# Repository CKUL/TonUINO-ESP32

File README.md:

# [TonUINO-ESP32](http://discourse.voss.earth/t/esp32-port-inkl-webinterface/399)
_[TonUINO V2.0](https://www.voss.earth/tonuino/) Code für ESP32 mit Erweiterungen, es gibt zu dem Projekt ebenfalls eine [Discourse Seite](http://discourse.voss.earth/)_

**Aktuell Umgesetzt:**
  
  - Webinterface zur Fernsteuerung
    - Play, Pause, Start, Stop, Lautstärke
    - Equalizer einstellen
    - max. Lautstärke einstellen
    - Ausschalttimer
    - Einschalttimer
    
  - Ambientlight mit WS2812 LED´s
    - ändern der Farbe über Webinterface
    
  - Timer zum Ein- und Ausschalten
    - Sonnenauf- und Untergang simulation für Einschalttimer
    - MP3-Wiedergabe beim Ein- / Ausschalten
    
  - AP-Modus um WLAN konfigurieren zu können ohne dies (SSID, PW) im Code fest zu verankern
    - Sprachansage bei Fehler mit der Verbindung
   
  - Begrüßung beim Einschalten 
   
  - Kopfhörererkennung
    - reduziert die Lautstärke wenn Kopfhörer gesteckt
    - begrenz die Lautstärke wenn Kopfhörer gesteckt
    - schaltet auf vorherige Lautstärke zurück wenn Kopfhörer nicht mehr gesteckt
    
  - Sprachmenü und Struktur auf Tag erweitert um Ambilight Farbe zu speichern
    
  - Funktion der Hoch- Runter- Tasten geändert
    - kurzes Drücken = Lautstärke +/-
    - langes Drücken = Lied +/-
    
 **Layout**

 **Noch offen und geplant:**
 
  - Speichern der Einstellungen im EEPROM / Flash
  - Tags verwalten

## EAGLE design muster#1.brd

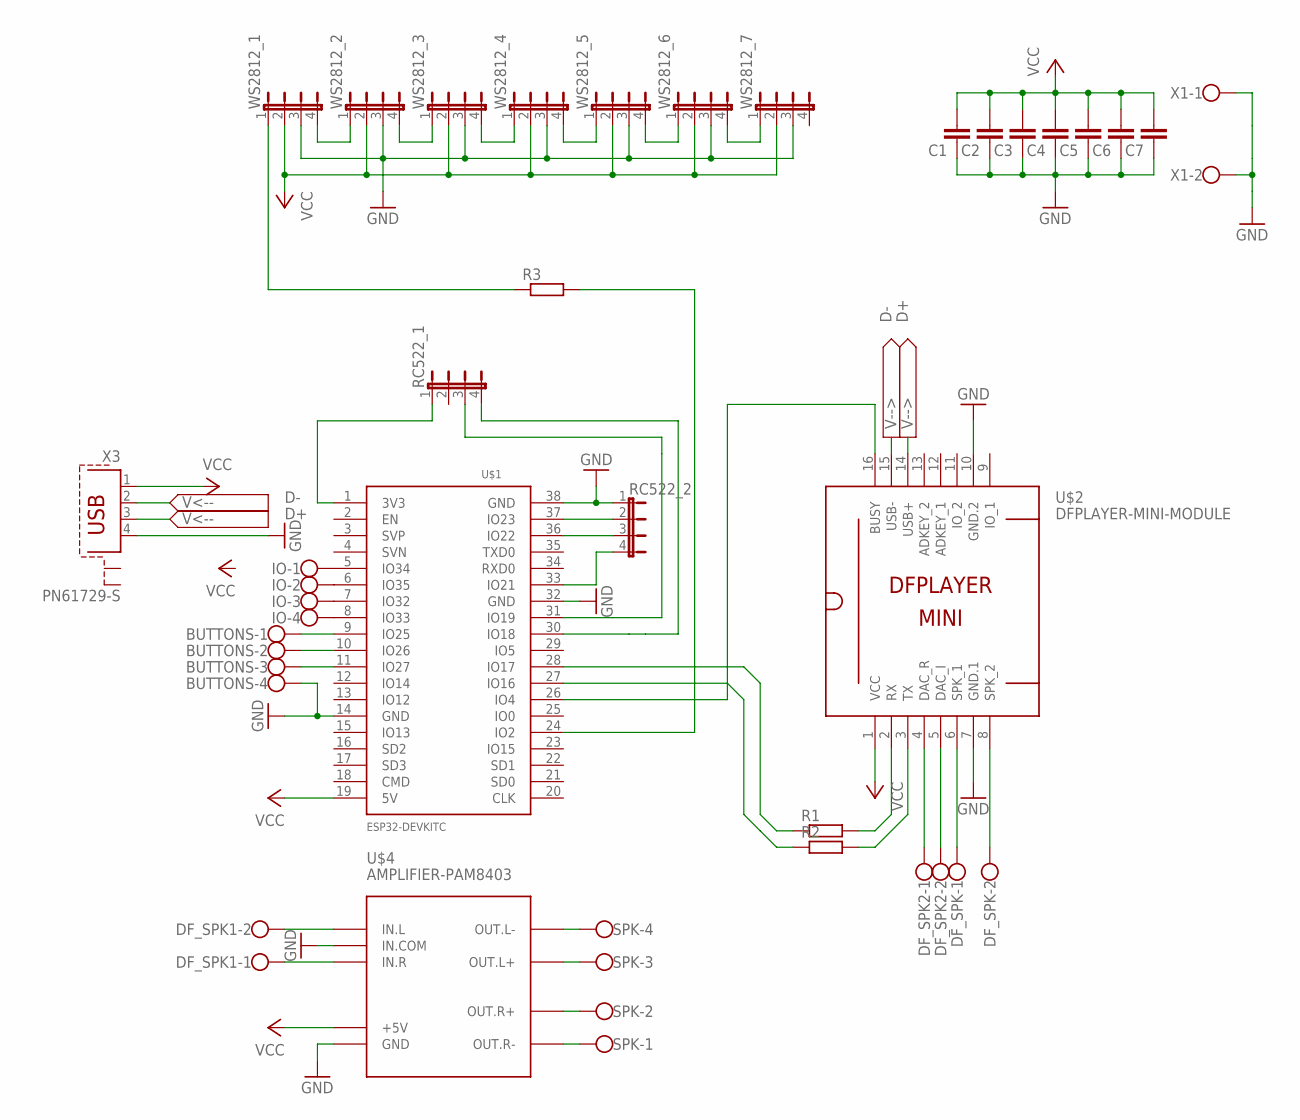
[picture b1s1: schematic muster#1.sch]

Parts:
BUTTONS: W237-4
C1: C-EU025-024X044; C025-024X044
C2, C3, C4, C5, C6, C7: C-EU025-025X050; C025-025X050
DF_SPK, DF_SPK1, DF_SPK2: W237-02P; W237-132
IO: W237-4
R1, R2, R3: R-EU_0204/2V; 0204V
RC522_1, RC522_2: JP4E; JP4
SPK: W237-4
U$1: ESP32DEVKITC; ESP32-DEVKITC
U$2: DFPLAYER-MINI-MODULE
U$4: AMPLIFIER-PAM8403
WS2812_1, WS2812_2, WS2812_3, WS2812_4, WS2812_5, WS2812_6, WS2812_7: JP4E; JP4
X1: W237-102
X3: PN61729-S

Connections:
D+: U$2.14 (USB+), X3.3
D-: U$2.15 (USB-), X3.2
GND: BUTTONS.4, C1.1, C2.1, C3.1, C4.1, C5.1, C6.1, C7.1, RC522_2.1, U$1.14 (GND), U$1.32 (GND), U$1.38 (GND), U$2.7 (GND.1), U$2.10 (GND.2), U$4.GND, U$4.IN.COM, WS2812_1.3, WS2812_2.3, WS2812_3.3, WS2812_4.3, WS2812_5.3, WS2812_6.3, WS2812_7.3, X1.1, X1.2, X3.4
unnamed: DF_SPK.2, U$2.8 (SPK_2)
unnamed: DF_SPK.1, U$2.6 (SPK_1)
unnamed: BUTTONS.1, U$1.9 (IO25)
unnamed: BUTTONS.2, U$1.10 (IO26)
unnamed: BUTTONS.3, U$1.11 (IO27)
unnamed: R1.1, U$1.28 (IO17)
unnamed: R2.1, U$1.27 (IO16)
unnamed: R2.2, U$2.3 (TX)
unnamed: WS2812_1.4, WS2812_2.1
unnamed: WS2812_2.4, WS2812_3.1
unnamed: R1.2, U$2.2 (RX)
unnamed: SPK.1, U$4.OUT.R-
unnamed: DF_SPK2.1, U$2.4 (DAC_R)
unnamed: R3.1, WS2812_1.1
unnamed: SPK.2, U$4.OUT.R+
unnamed: SPK.3, U$4.OUT.L+
unnamed: SPK.4, U$4.OUT.L-
unnamed: WS2812_3.4, WS2812_4.1
unnamed: WS2812_4.4, WS2812_5.1
unnamed: WS2812_5.4, WS2812_6.1
unnamed: WS2812_6.4, WS2812_7.1
unnamed: DF_SPK2.2, U$2.5 (DAC_I)
unnamed: DF_SPK1.2, U$4.IN.L
unnamed: DF_SPK1.1, U$4.IN.R
unnamed: R3.2, U$1.24 (IO2)
unnamed: RC522_2.2, U$1.37 (IO23)
unnamed: U$1.26 (IO4), U$2.16 (BUSY)
unnamed: RC522_2.3, U$1.36 (IO22)
unnamed: RC522_2.4, U$1.33 (IO21)
unnamed: RC522_1.3, U$1.31 (IO19)
unnamed: RC522_1.4, U$1.30 (IO18)
unnamed: RC522_1.1, U$1.1 (3V3)
unnamed: IO.1, U$1.5 (IO34)
unnamed: IO.2, U$1.6 (IO35)
unnamed: IO.3, U$1.7 (IO32)
unnamed: IO.4, U$1.8 (IO33)
VCC: C1.2, C2.2, C3.2, C4.2, C5.2, C6.2, C7.2, U$1.19 (5V), U$2.1 (VCC), U$4.+5V, WS2812_1.2, WS2812_2.2, WS2812_3.2, WS2812_4.2, WS2812_5.2, WS2812_6.2, WS2812_7.2, X3.1

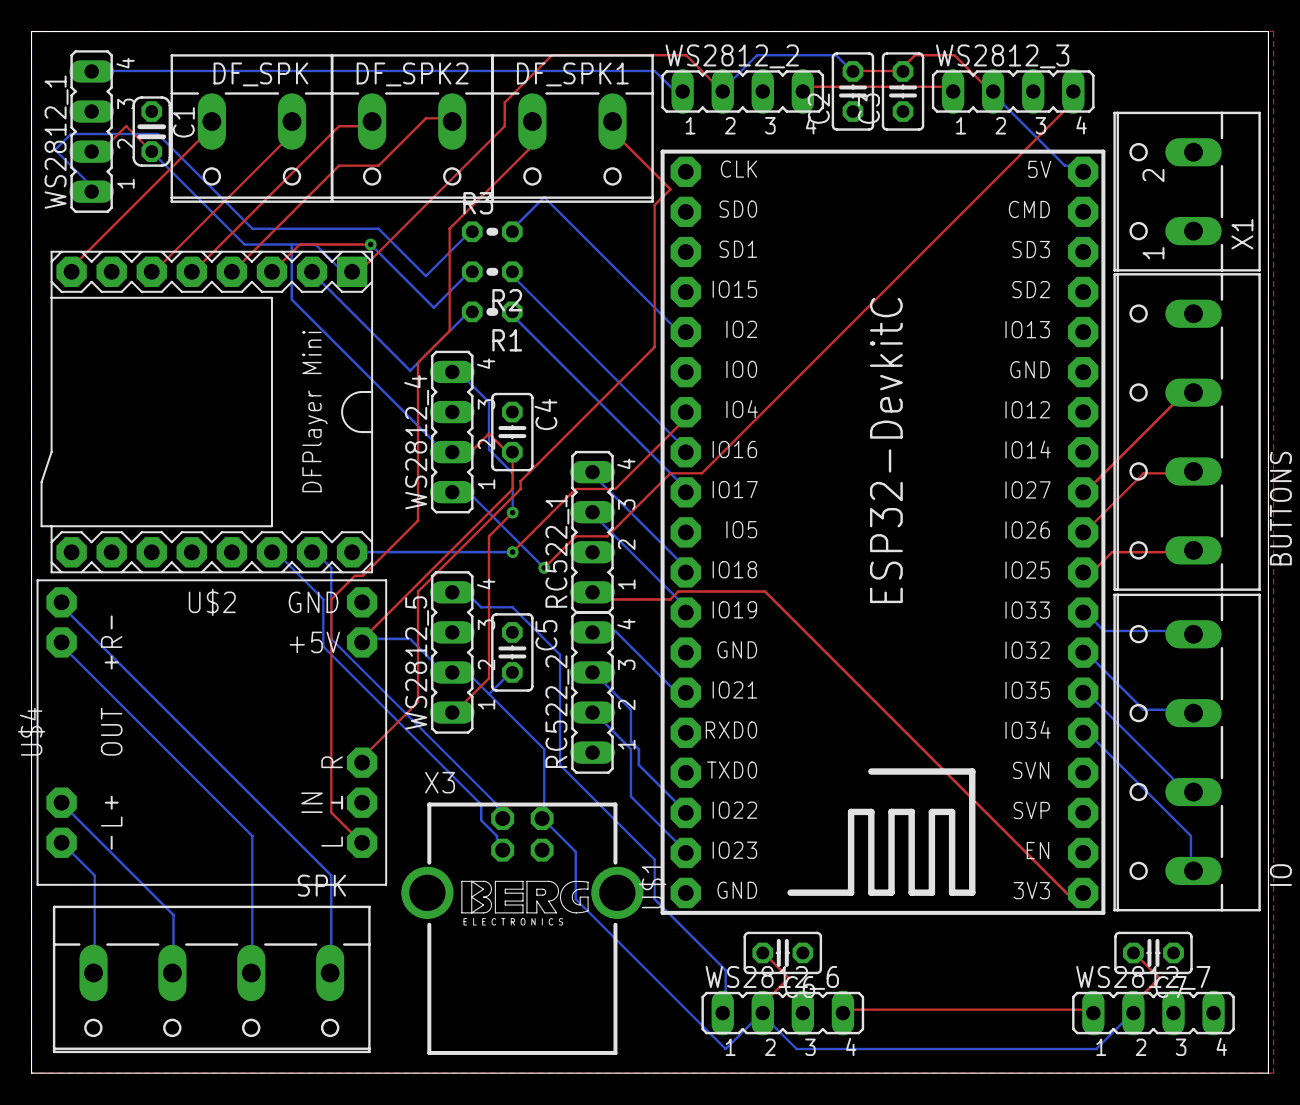
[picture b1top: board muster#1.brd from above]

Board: 2 copper layers, 78.4 x 66.0 mm, 30 parts (0 on the bottom side), 40 nets.

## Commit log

2018-12-02 Under Construction
2018-12-04 erstes Leiterplattendesign
2018-12-05 neuen Ordner angelegt
2018-12-05 beschreibung erweitert
2018-12-05 Formatierung angepasst
2018-12-05 Links zur ofiziellen TonUINO Seite eingepflegt
2018-12-05 neuer Link
2018-12-07 Sprachmenü erweitert zum Speichern der Ambilightfarbe auf dem RFID-Tag
2018-12-07 anpassung wegen Softwareänderung
2018-12-07 anpassung nach Code änderung
2018-12-22 neue Funktionen
    + WiFi-AP zum Einrichten des WLAN
    + Begrüßung beim Starten der Box
    + Jingles für Timer
    + Ansage bei WLAN Fehler
2018-12-22 neue Seite
    Seite zum Einrichten des WLAN und Neu-Starten der Box
2018-12-22 Anpassung bezüglich neuer Funktionen
2018-12-26 Added friting layout
2018-12-26 added layout image to README.md
2018-12-26 Added header file and hostname support
2018-12-28 Added OTA update possibility

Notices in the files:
parts and their libraries:
diy-modules: Released under the Creative Commons Attribution 4.0 International License: http://creativecommons.org/licenses/by/4.0
